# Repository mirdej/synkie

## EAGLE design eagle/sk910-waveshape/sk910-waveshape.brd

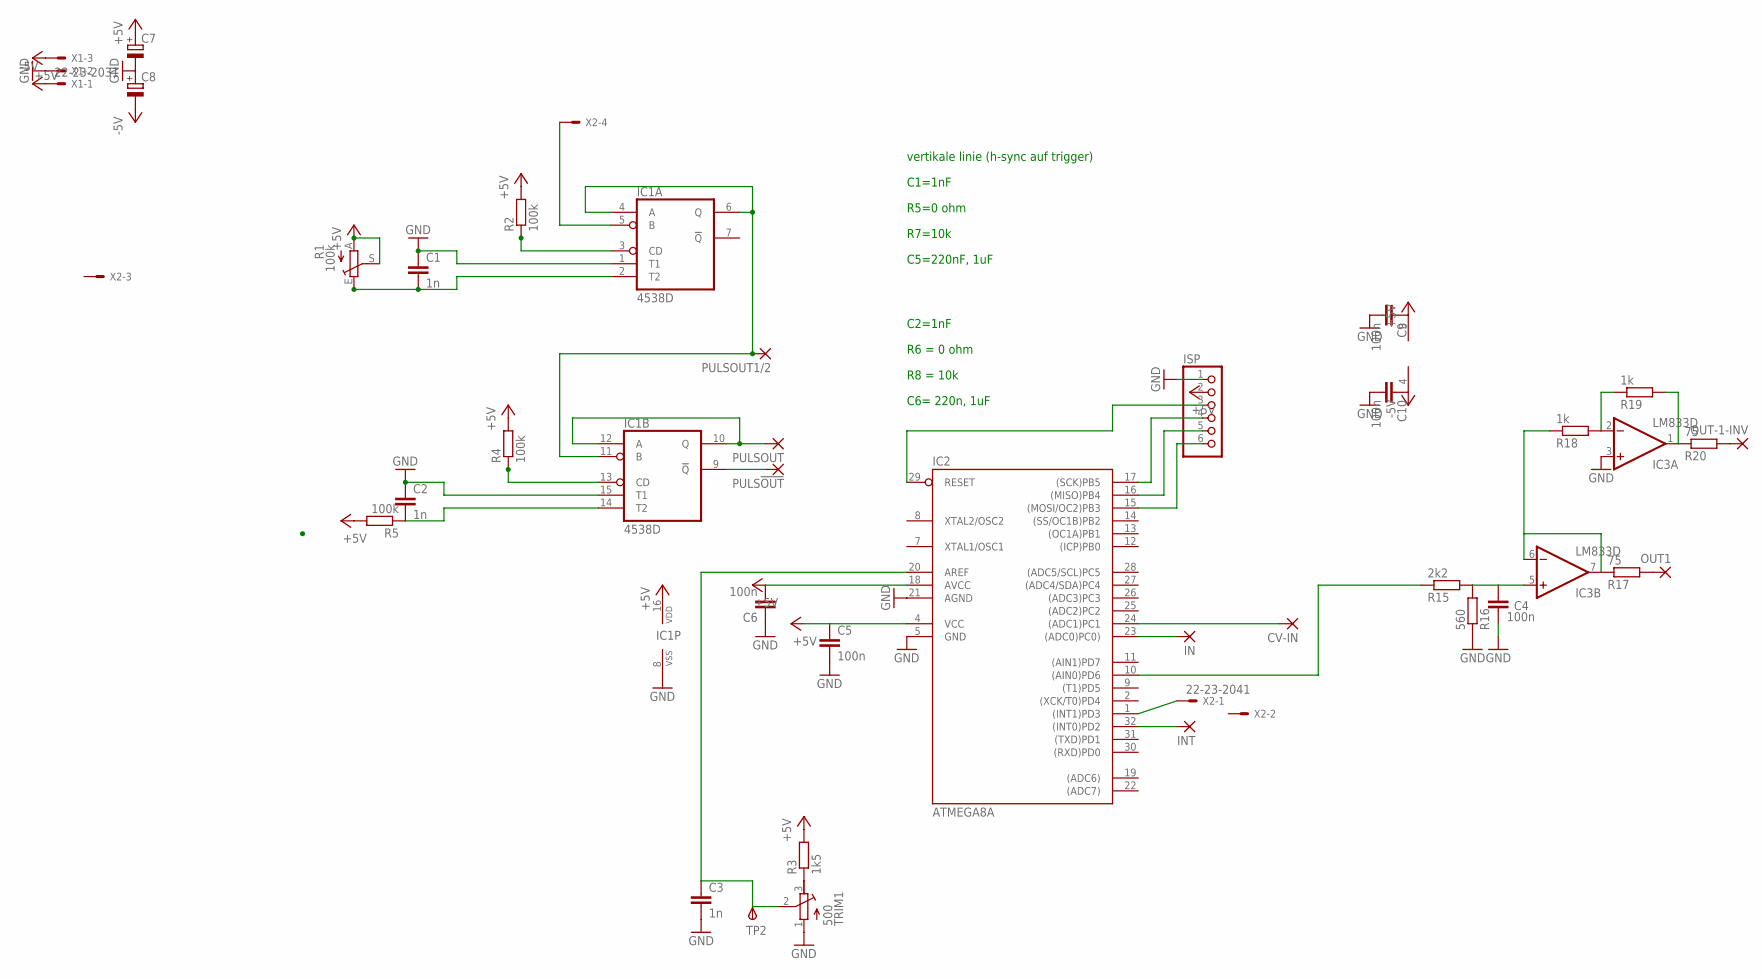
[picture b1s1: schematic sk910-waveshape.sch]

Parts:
C1, C2, C3: 1n; C1206
C4: 100n; C0805
C5: 100n; C1206
C6, C9, C10: 100n; C0603
C7, C8: CPOL-EUCT6032; CT6032
CV-IN: 3,17/1,1
IC1: 4538D; SO16
IC2: ATMEGA8A; TQFP32-08
IC3: LM833D; SO08
IN: 3,17/1,1
INT: 3,17/1,1
ISP: PINHD-1X6; 1X06
OUT1: 3,17/1,1
OUT-1-INV: 3,17/1,1
PULS!OUT: 3,17/1,1
PULSOUT, PULSOUT1/2: 3,17/1,1
R1: 100k; CIP20C-6MM
R2, R4, R5: 100k; R1206
R3: 1k5; R1206
R15: 2k2; R1206
R16: 560; R1206
R17, R20: 75; R1206
R18, R19: 1k; R1206
TP2: TPSPAD1-13; P1-13
TRIM1: 500; RTRIM64Y
X1: 22-23-2031
X2: 22-23-2041

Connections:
+5V: C2.2, C5.1, C6.2, C7.+, C9.1, IC1.14 (T2), IC1.16 (VDD), IC2.4 (VCC), IC2.18 (AVCC), IC3.8 (V+), ISP.2, R1.A, R1.S, R2.2, R3.2, R4.2, R5.1, R5.2, X1.3
-5V: C8.-, C10.1, IC3.4 (V-), X1.1
GND: C1.1, C2.1, C3.2, C4.2, C5.2, C6.1, C7.-, C8.+, C9.2, C10.2, IC1.1 (T1), IC1.8 (VSS), IC1.15 (T1), IC2.5 (GND), IC2.21 (AGND), IC3.3 (+IN), ISP.1, R16.1, TRIM1.1 (E), X1.2
unnamed: IC1.3 (CD), R2.1
unnamed: IC2.32 ((INT0)PD2), INT.1
unnamed: IC1.10 (Q), IC1.12 (A), PULSOUT.1
unnamed: IC1.4 (A), IC1.6 (Q), IC1.11 (B), PULSOUT1/2.1
unnamed: IC2.23 ((ADC0)PC0)), IN.1
unnamed: C1.2, IC1.2 (T2), R1.E
unnamed: IC2.1 ((INT1)PD3), X2.1
unnamed: R3.1, TRIM1.3 (A)
unnamed: CV-IN.1, IC2.24 ((ADC1)PC1)
unnamed: IC2.29 (RESET), ISP.3
unnamed: IC2.17 ((SCK)PB5), ISP.4
unnamed: IC1.13 (CD), R4.1
unnamed: IC1.9 (!Q), PULS!OUT.1
unnamed: IC2.16 ((MISO)PB4), ISP.5
unnamed: IC2.15 ((MOSI/OC2)PB3), ISP.6
unnamed: IC1.5 (B), X2.4
unnamed: IC2.10 ((AIN0)PD6), R15.1
unnamed: C4.1, IC3.5 (+IN), R15.2, R16.2
unnamed: IC3.6 (-IN), IC3.7 (OUT), R17.1, R18.1
unnamed: IC3.2 (-IN), R18.2, R19.1
unnamed: OUT-1-INV.1, R20.2
unnamed: OUT1.1, R17.2
unnamed: IC3.1 (OUT), R19.2, R20.1
unnamed: C3.1, IC2.20 (AREF), TP2.TP, TRIM1.2 (S)

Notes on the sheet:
vertikale linie (h-sync auf trigger)
C1=1nF
R5=0 ohm
R7=10k
C5=220nF, 1uF
C2=1nF
R6 = 0 ohm
R8 = 10k
C6= 220n, 1uF

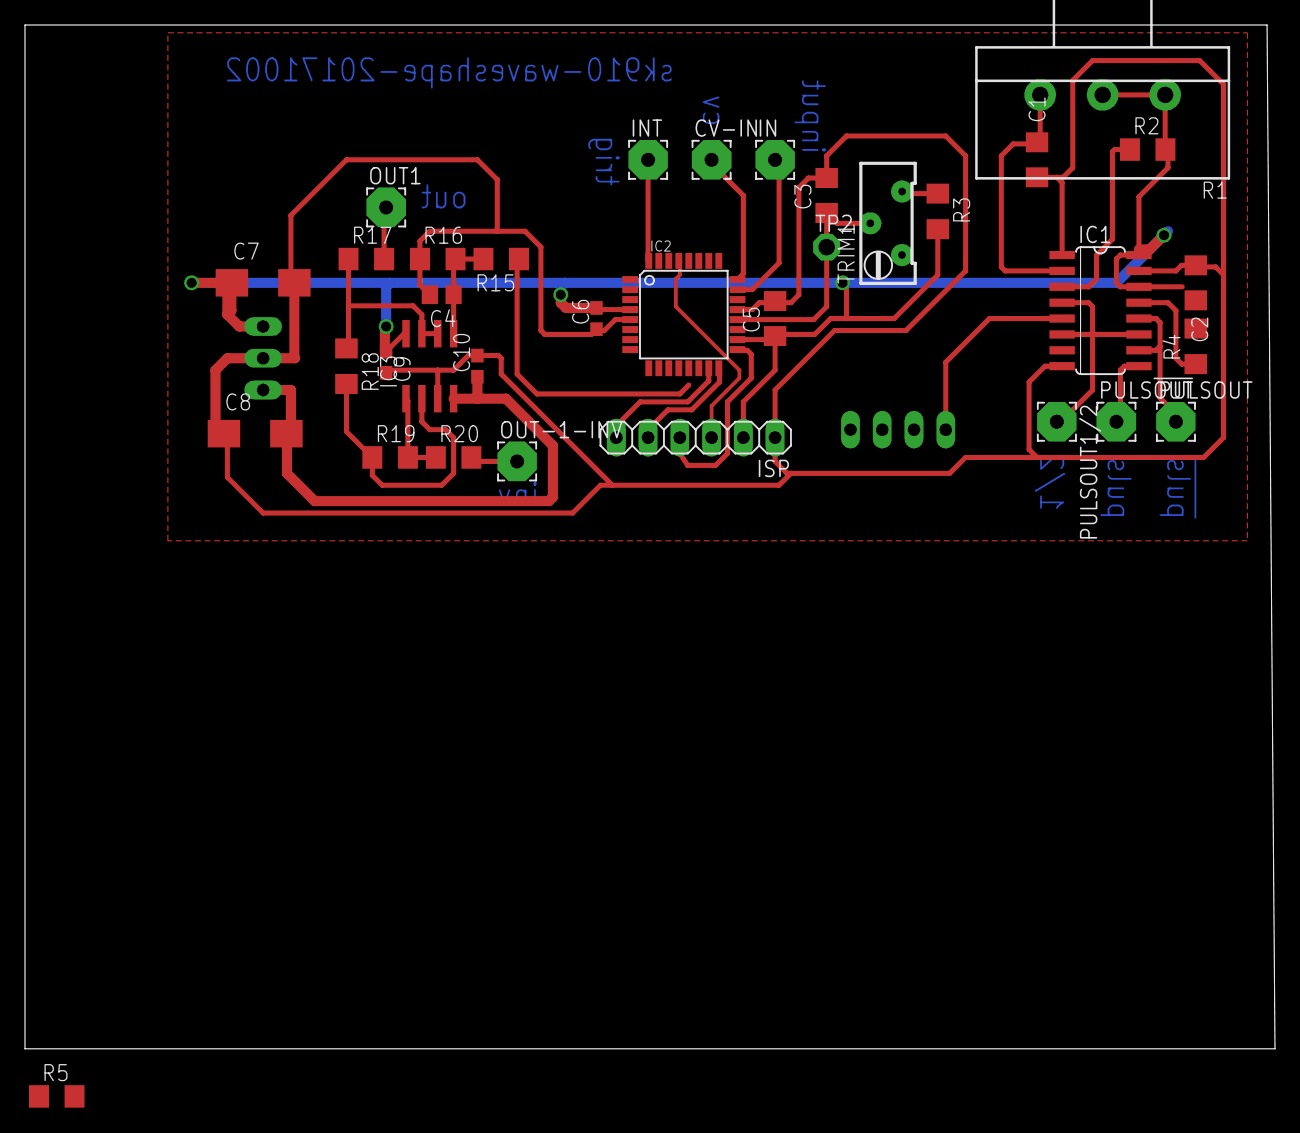
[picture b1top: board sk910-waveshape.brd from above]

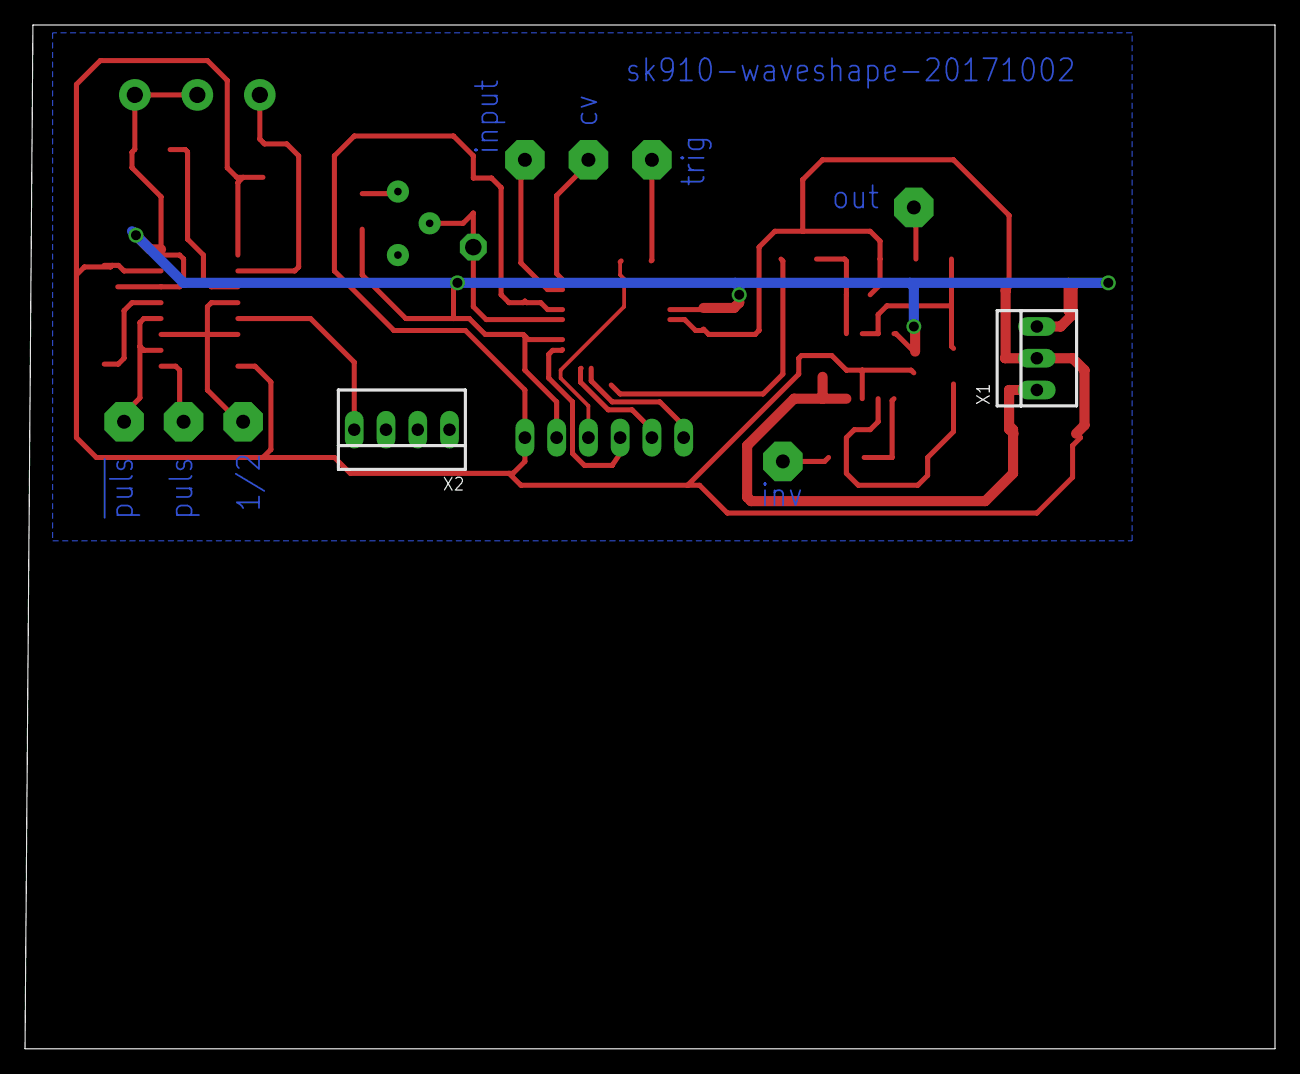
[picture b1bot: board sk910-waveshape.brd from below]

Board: 2 copper layers, 100.0 x 81.9 mm, 37 parts (2 on the bottom side), 27 nets.

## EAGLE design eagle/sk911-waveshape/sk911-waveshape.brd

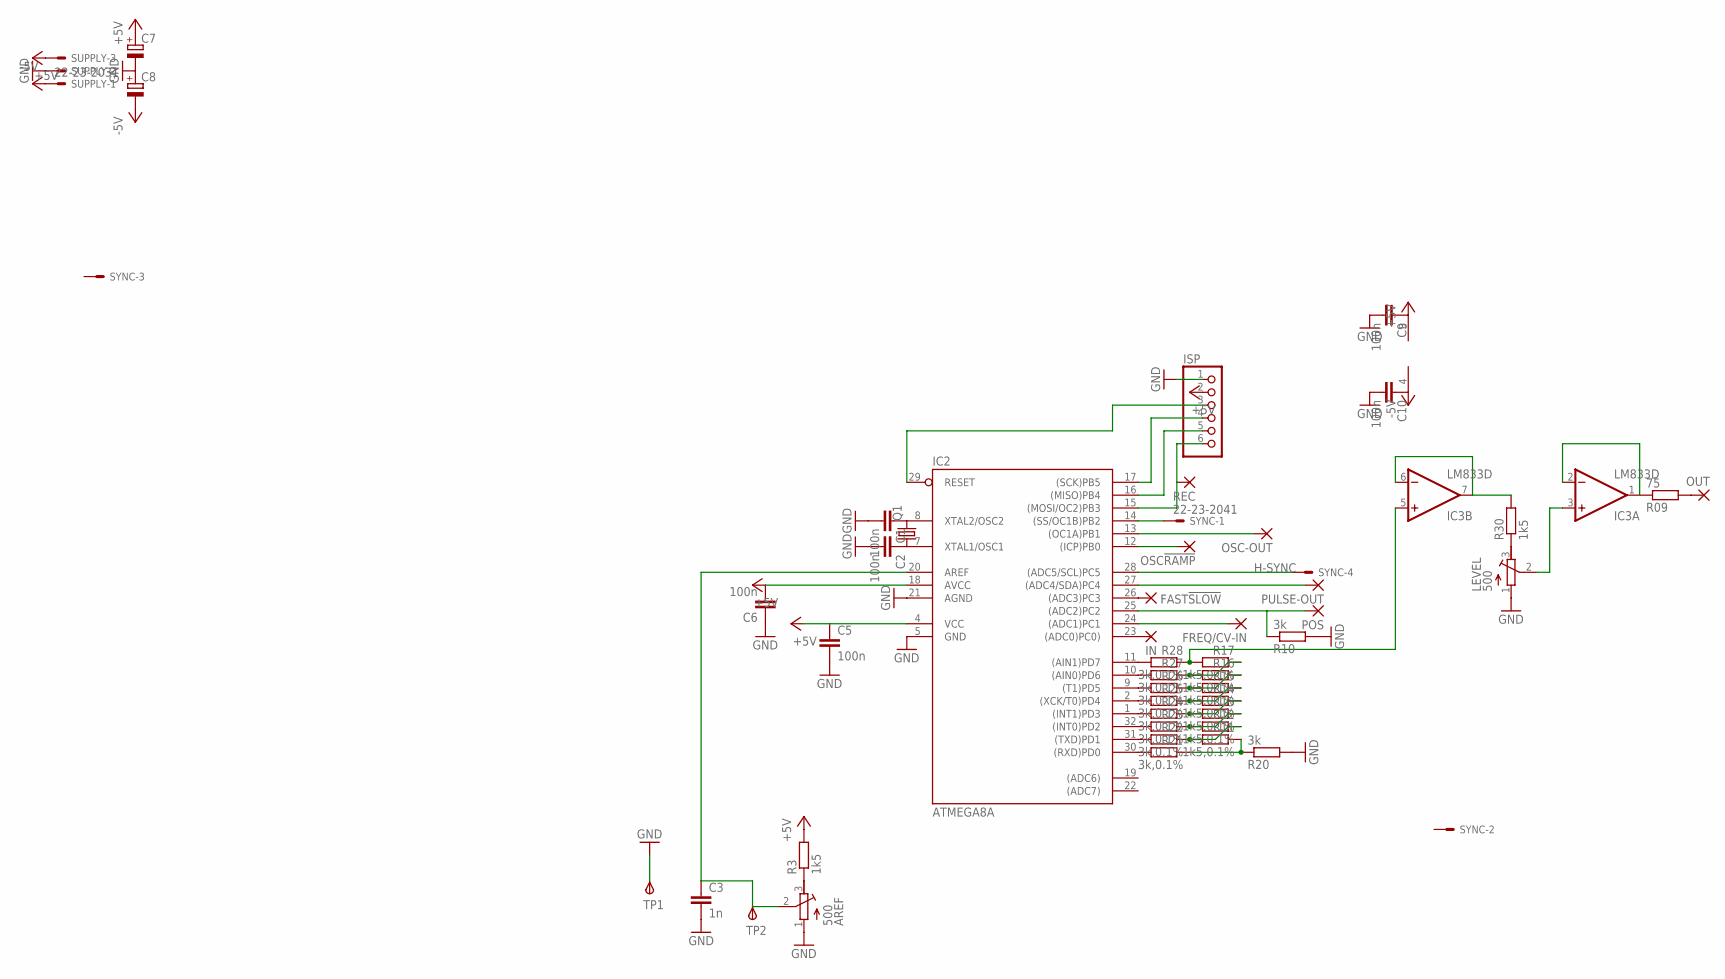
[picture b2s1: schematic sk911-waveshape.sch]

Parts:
AREF: 500; RTRIM64Y
C1, C2: 100n; C0805
C3: 1n; C1206
C5, C6, C9, C10: 100n; C0603
C7, C8: CPOL-EUCT6032; CT6032
FAST!SLOW: 3,17/1,1
FREQ/CV-IN: 3,17/1,1
IC2: ATMEGA8A; TQFP32-08
IC3: LM833D; SO08
IN: 3,17/1,1
ISP: PINHD-1X6; 1X06
LEVEL: 500; RTRIM64Y
OSC!RAMP: 3,17/1,1
OSC-OUT: 3,17/1,1
OUT: 3,17/1,1
POS: 3,17/1,1
PULSE-OUT: 3,17/1,1
Q1: CRYSTALHC49UP; HC49UP
R3, R30: 1k5; R1206
R09: 75; R1206
R10: 3k; R1206
R11, R12, R13, R14, R15, R16, R17: 1k5,0.1%; R0603
R20: 3k; R0603
R21, R22, R23, R24, R25, R26, R27, R28: 3k,0.1%; R0603
REC: 3,17/1,1
SUPPLY: 22-23-2031
SYNC: 22-23-2041
TP1, TP2: TPSPAD1-13; P1-13

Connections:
+5V: C5.1, C6.2, C7.+, C9.1, IC2.4 (VCC), IC2.18 (AVCC), IC3.8 (V+), ISP.2, R3.2, SUPPLY.3
-5V: C8.-, C10.1, IC3.4 (V-), SUPPLY.1
GND: AREF.1 (E), C1.2, C2.2, C3.2, C5.2, C6.1, C7.-, C8.+, C9.2, C10.2, IC2.5 (GND), IC2.21 (AGND), ISP.1, LEVEL.1 (E), R10.2, R20.2, SUPPLY.2, TP1.TP
H-SYNC: IC2.28 ((ADC5/SCL)PC5), SYNC.4
unnamed: C1.1, IC2.8 (XTAL2/OSC2), Q1.2
unnamed: IC2.25 ((ADC2)PC2), POS.1, R10.1
unnamed: C2.1, IC2.7 (XTAL1/OSC1), Q1.1
unnamed: IC2.31 ((TXD)PD1), R22.2
unnamed: IC2.23 ((ADC0)PC0)), IN.1
unnamed: IC2.1 ((INT1)PD3), R24.2
unnamed: IC2.2 ((XCK/T0)PD4), R25.2
unnamed: AREF.3 (A), R3.1
unnamed: FREQ/CV-IN.1, IC2.24 ((ADC1)PC1)
unnamed: IC2.29 (RESET), ISP.3
unnamed: IC2.17 ((SCK)PB5), ISP.4
unnamed: IC2.9 ((T1)PD5), R26.2
unnamed: IC2.10 ((AIN0)PD6), R27.2
unnamed: IC2.16 ((MISO)PB4), ISP.5
unnamed: IC2.15 ((MOSI/OC2)PB3), ISP.6, REC.1
unnamed: IC2.11 ((AIN1)PD7), R28.2
unnamed: IC2.30 ((RXD)PD0), R21.2
unnamed: IC2.13 ((OC1A)PB1), OSC-OUT.1
unnamed: IC2.12 ((ICP)PB0), OSC!RAMP.1
unnamed: IC2.32 ((INT0)PD2), R23.2
unnamed: R11.2, R12.1, R22.1
unnamed: R11.1, R20.1, R21.1
unnamed: R12.2, R13.1, R23.1
unnamed: R13.2, R14.1, R24.1
unnamed: R14.2, R15.1, R25.1
unnamed: R15.2, R16.1, R26.1
unnamed: R16.2, R17.1, R27.1
unnamed: IC3.5 (+IN), R17.2, R28.1
unnamed: IC3.6 (-IN), IC3.7 (OUT), R30.2
unnamed: LEVEL.3 (A), R30.1
unnamed: IC3.1 (OUT), IC3.2 (-IN), R09.1
unnamed: IC3.3 (+IN), LEVEL.2 (S)
unnamed: FAST!SLOW.1, IC2.26 ((ADC3)PC3)
unnamed: IC2.27 ((ADC4/SDA)PC4), PULSE-OUT.1
unnamed: OUT.1, R09.2
unnamed: AREF.2 (S), C3.1, IC2.20 (AREF), TP2.TP
ODD!EVEN: IC2.14 ((SS/OC1B)PB2), SYNC.1

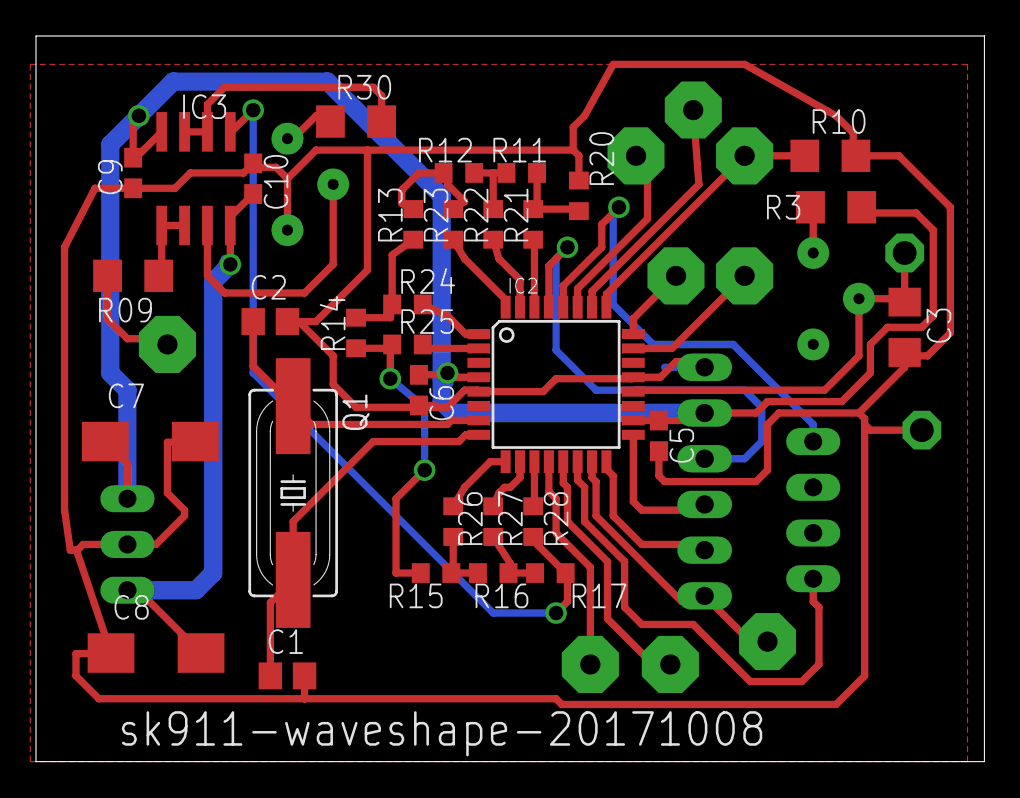
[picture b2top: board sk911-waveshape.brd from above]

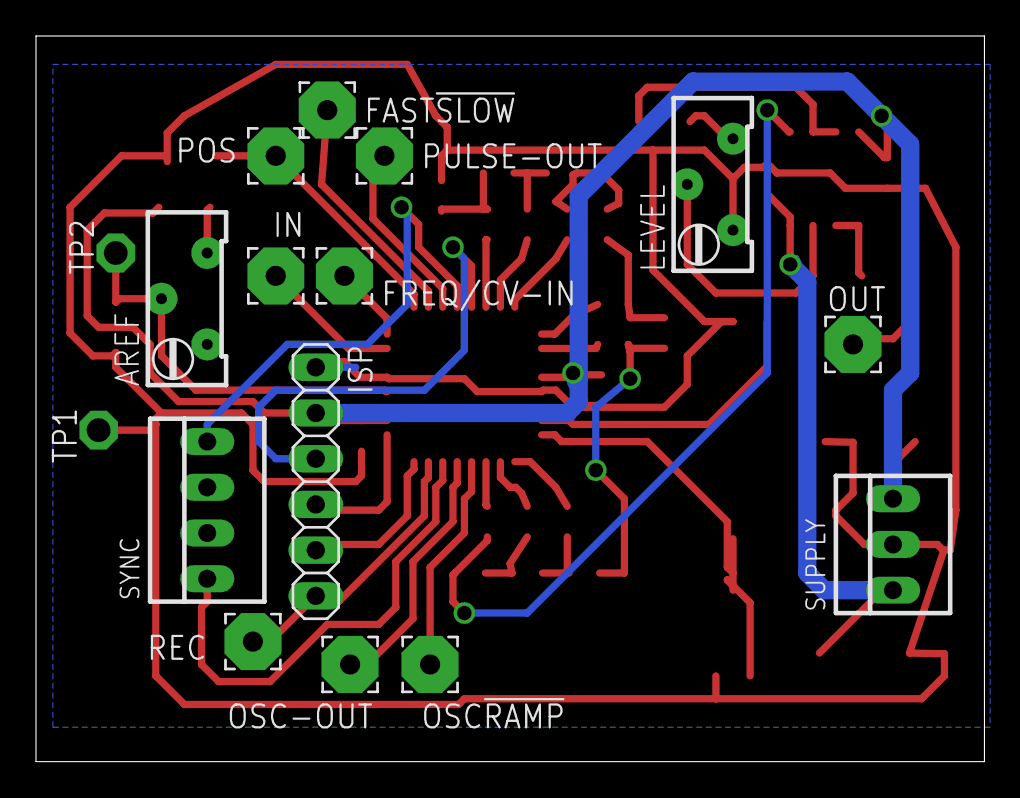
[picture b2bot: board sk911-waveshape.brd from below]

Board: 2 copper layers, 52.7 x 40.3 mm, 48 parts (16 on the bottom side), 41 nets.

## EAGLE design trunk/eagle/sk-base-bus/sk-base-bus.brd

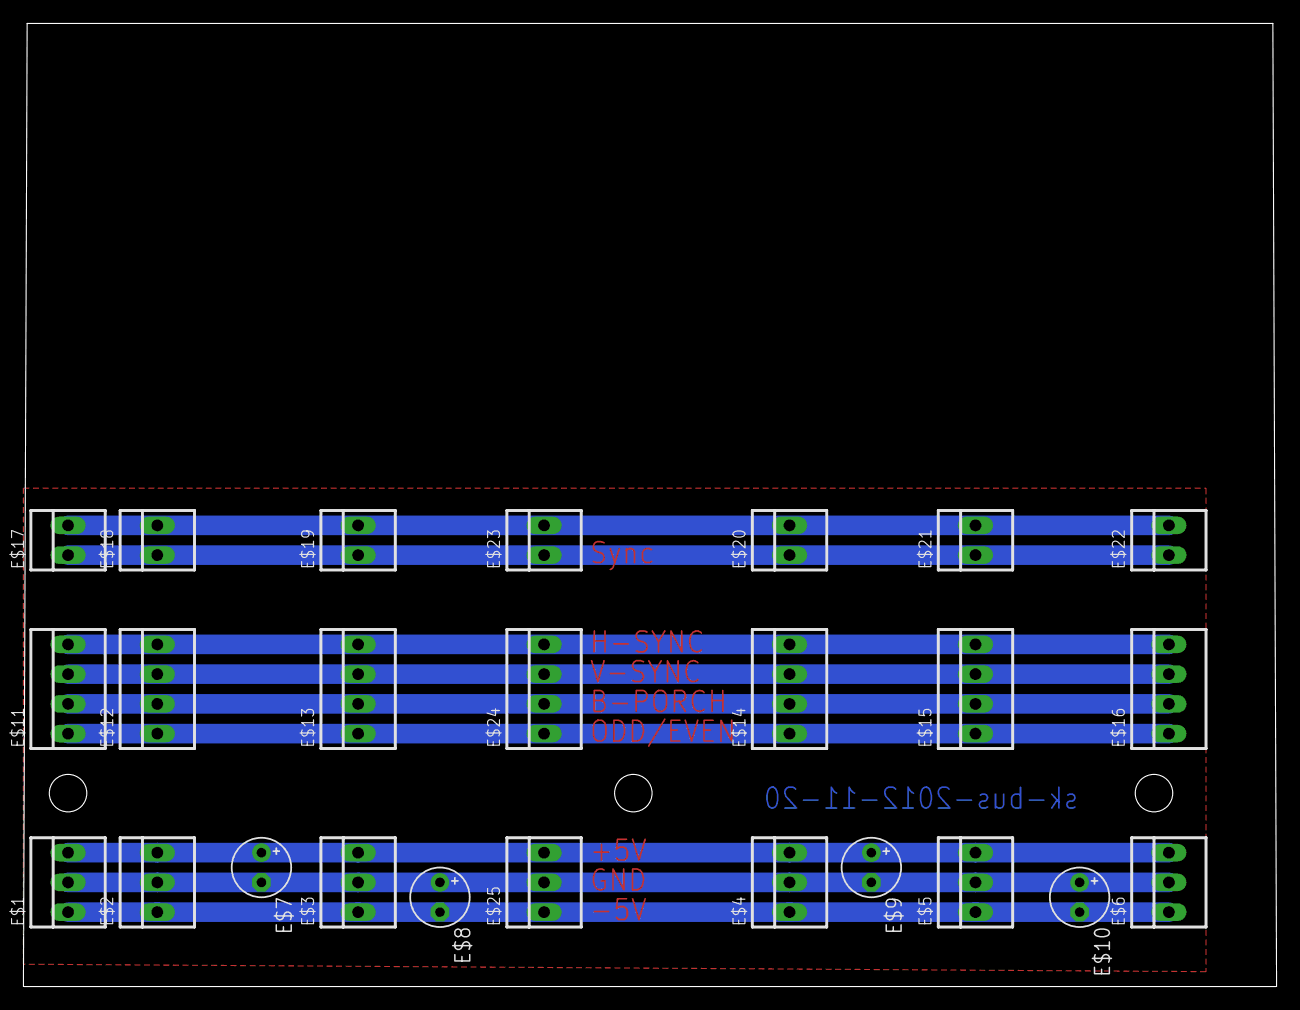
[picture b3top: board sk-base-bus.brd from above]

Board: 2 copper layers, 107.0 x 82.2 mm, 25 parts (0 on the bottom side), 9 nets.

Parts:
E$1, E$2, E$3, E$4, E$5, E$6, E$25: 22-23-2031
E$7, E$8, E$9, E$10: E2,5-5
E$11, E$12, E$13, E$14, E$15, E$16, E$24: 22-23-2041
E$17, E$18, E$19, E$20, E$21, E$22, E$23: 22-23-2021

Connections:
AGND: E$17.2, E$18.2, E$19.2, E$20.2, E$21.2, E$22.2
GND: E$1.2, E$2.2, E$3.2, E$4.2, E$5.2, E$6.2
S$1: E$1.3, E$2.3, E$3.3, E$4.3, E$5.3, E$6.3
S$3: E$1.1, E$2.1, E$3.1, E$4.1, E$5.1, E$6.1
S$5: E$11.4, E$12.4, E$13.4, E$14.4, E$15.4, E$16.4
S$6: E$11.3, E$12.3, E$13.3, E$14.3, E$15.3, E$16.3
S$7: E$11.2, E$12.2, E$13.2, E$14.2, E$15.2, E$16.2
S$8: E$11.1, E$12.1, E$13.1, E$14.1, E$15.1, E$16.1
S$10: E$17.1, E$18.1, E$19.1, E$20.1, E$21.1, E$22.1

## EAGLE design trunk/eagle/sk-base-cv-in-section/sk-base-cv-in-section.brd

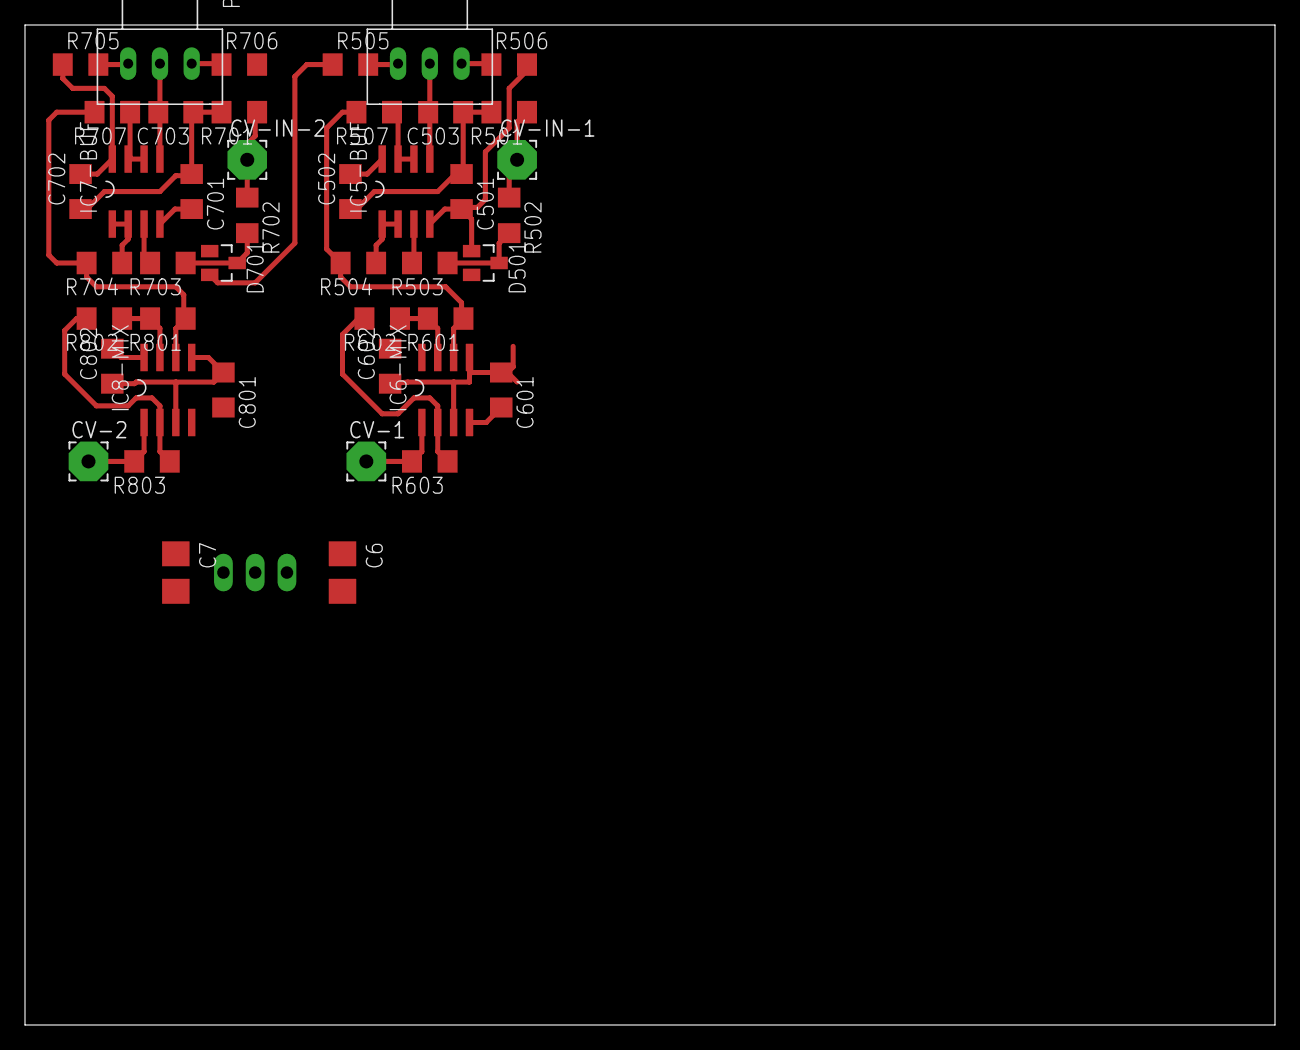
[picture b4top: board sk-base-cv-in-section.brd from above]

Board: 2 copper layers, 100.0 x 80.0 mm, 45 parts (1 on the bottom side), 27 nets.

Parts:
C6, C7: 2u2tantal; CT3528
C501, C502, C503, C601, C602, C701, C702, C703, C801, C802: C1206
CV-1, CV-2: 3,17/1,1
CV-IN-1, CV-IN-2: 3,17/1,1
D501, D701: BAT54S-L44; SOT23
IC5-BUF, IC6-MIX, IC7-BUF, IC8-MIX: MAX4392ESA; SO08
POT10K1: 10k; ALPS_RK09K111
R501, R701: 47k; R1206
R502, R503, R702, R703: 100; R1206
R504, R507, R601, R602, R603, R704, R707, R801, R802, R803: 4k7; R1206
R505, R506, R705, R706: 20k; R1206
U$1: ALPS_RK09K111_HOHNE-FüSSE; ALPS_RK09K111
X1: 22-23-2031

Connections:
+5V: C6.+, C502.2, C602.2, C702.2, C802.2, D501.2, D701.2, IC5-BUF.8, IC6-MIX.8, IC7-BUF.8, IC8-MIX.8, R505.1, R705.1, X1.3
-5V: C7.-, C501.2, C601.2, C701.2, C801.2, D501.1, D701.1, IC5-BUF.4, IC6-MIX.4, IC7-BUF.4, IC8-MIX.4, R506.2, R706.2, X1.1
GND: C6.-, C7.+, C501.1, C502.1, C503.1, C601.1, C602.1, C701.1, C702.1, C703.1, C801.1, C802.1, IC6-MIX.3, IC6-MIX.5, IC8-MIX.3, IC8-MIX.5, R501.2, R701.2, X1.2
unnamed: C503.2, IC5-BUF.5, U$1.2
unnamed: R506.1, U$1.1
unnamed: R505.2, U$1.3
unnamed: CV-IN-1.1, R501.1, R502.1
unnamed: D501.3, R502.2, R503.1
unnamed: IC5-BUF.6, IC5-BUF.7, R507.1
unnamed: IC5-BUF.3, R503.2
unnamed: IC5-BUF.1, IC5-BUF.2, R504.1
unnamed: IC6-MIX.6, R504.2, R507.2, R601.1
unnamed: IC6-MIX.7, R601.2, R602.1
unnamed: IC6-MIX.2, R602.2, R603.1
unnamed: CV-1.1, IC6-MIX.1, R603.2
unnamed: CV-IN-2.1, R701.1, R702.1
unnamed: D701.3, R702.2, R703.1
unnamed: IC7-BUF.3, R703.2
unnamed: IC7-BUF.1, IC7-BUF.2, R704.1
unnamed: IC7-BUF.6, IC7-BUF.7, R707.1
unnamed: IC8-MIX.6, R704.2, R707.2, R801.1
unnamed: IC8-MIX.7, R801.2, R802.1
unnamed: IC8-MIX.2, R802.2, R803.1
unnamed: CV-2.1, IC8-MIX.1, R803.2
unnamed: C703.2, IC7-BUF.5, POT10K1.2
unnamed: POT10K1.1, R706.1
unnamed: POT10K1.3, R705.2

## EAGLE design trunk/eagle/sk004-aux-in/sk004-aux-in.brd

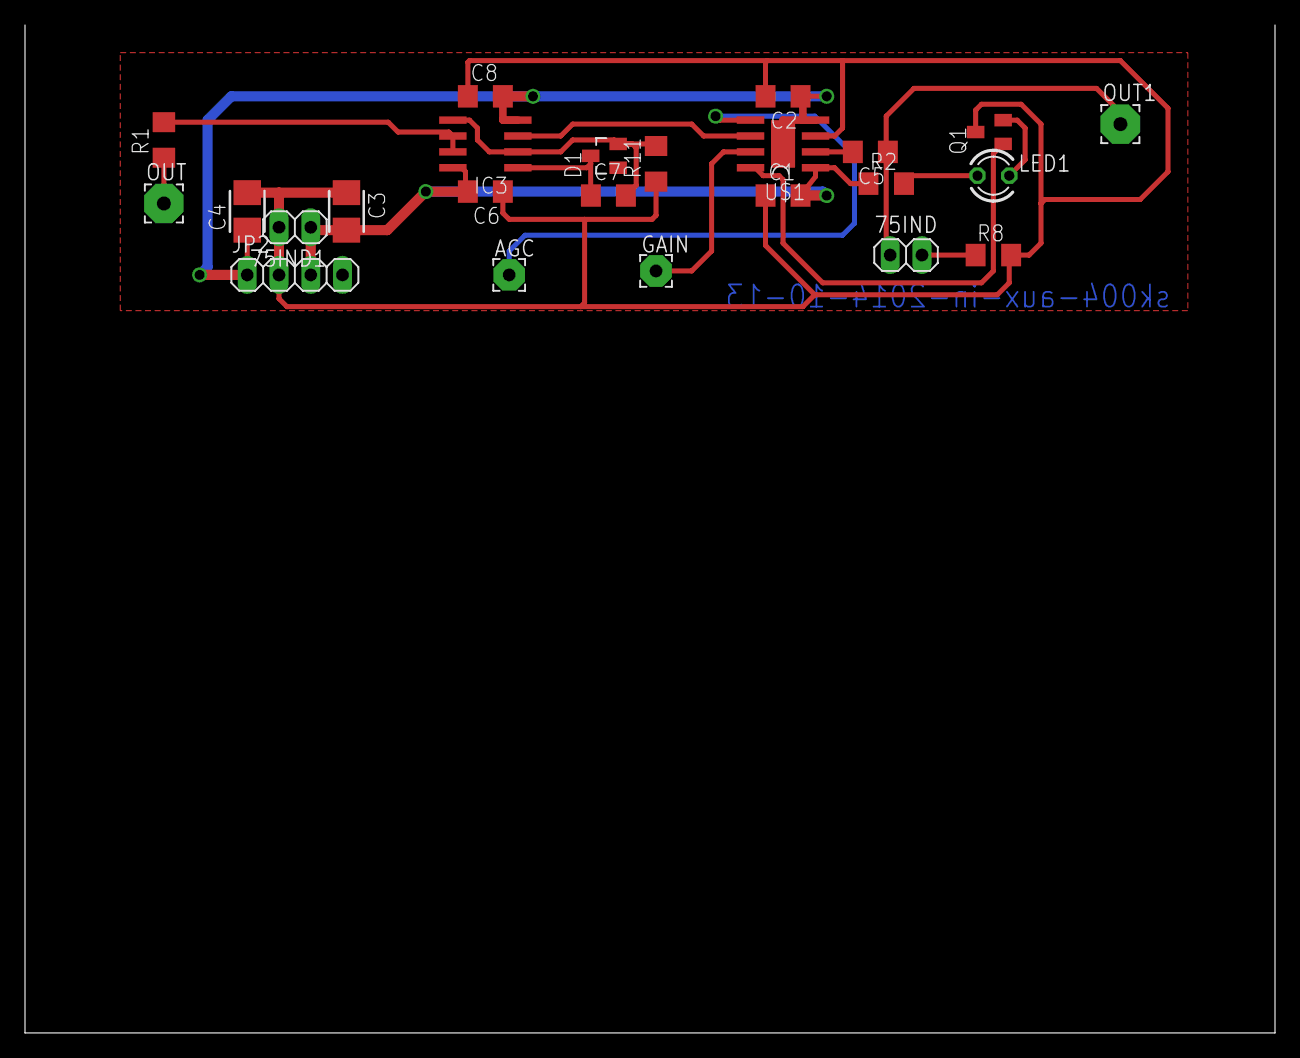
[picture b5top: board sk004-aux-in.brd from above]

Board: 2 copper layers, 100.0 x 80.6 mm, 24 parts (0 on the bottom side), 16 nets.

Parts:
75IND, 75IND1: 1X02
AGC: 2,54/1,0
C1, C2: C1206
C3, C4: 2u2tantal; CT3528
C5: 1u; C1206
C6, C8: 100n; C1206
C7: 10p; C1206
D1: BAT54S-L44; SOT23
GAIN: 2,54/1,0
IC3: LM833D; SO08
JP2: 1X04
LED1: LED3MM
OUT, OUT1: 3,17/1,1
Q1: BC857ASMD; SOT23-BEC
R1, R8: 75; R1206
R2: 300; R1206
R11: 1k; R1206
U$1: MAX7450; SO08-EXP

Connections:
+5V: 75IND1.1, C1.2, C3.+, C6.2, IC3.8, JP2.3, R2.1, U$1.1
-5V: C2.1, C4.-, C8.2, IC3.4, JP2.1, U$1.4, U$1.EXP
GND: 75IND1.2, C1.1, C2.2, C3.-, C4.+, C6.1, C8.1, JP2.2, Q1.C, R8.2, R11.1, U$1.3
unnamed: 75IND.2, R8.1
unnamed: 75IND.1, C5.1, OUT1.1
unnamed: IC3.3, U$1.6
unnamed: GAIN.1, U$1.7
unnamed: AGC.1, U$1.5
unnamed: LED1.A, R2.2
unnamed: Q1.B, U$1.8
unnamed: C5.2, U$1.2
unnamed: LED1.K, Q1.E
unnamed: IC3.6, IC3.7, R1.2
unnamed: OUT.1, R1.1
unnamed: C7.1, D1.3, IC3.1
unnamed: C7.2, D1.2, IC3.2, IC3.5, R11.2

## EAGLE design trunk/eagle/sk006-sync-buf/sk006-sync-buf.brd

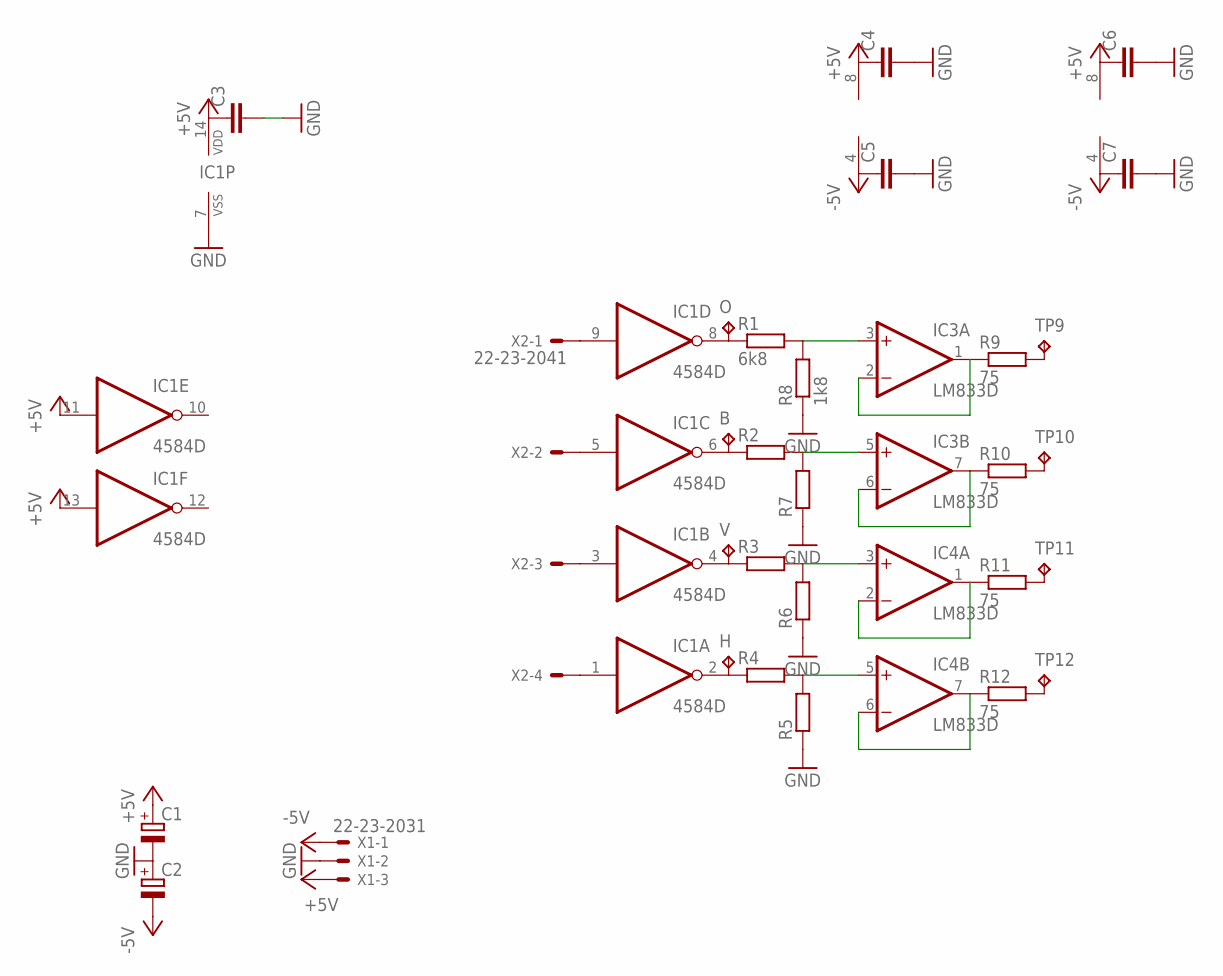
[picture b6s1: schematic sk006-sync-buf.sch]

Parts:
B: TPB2,54; B2,54
C1, C2: CPOL-EUE2.5-7; E2,5-7
C3, C4, C5, C6, C7: C-EUC1206; C1206
H: TPB2,54; B2,54
IC1: 4584D; SO14
IC3, IC4: LM833D; SO08
O: TPB2,54; B2,54
R1: 6k8; R1206
R2, R3, R4, R5, R6, R7: R-EU_R1206; R1206
R8: 1k8; R1206
R9, R10, R11, R12: 75; R1206
TP9, TP10, TP11, TP12: TPB2,54; B2,54
V: TPB2,54; B2,54
X1: 22-23-2031
X2: 22-23-2041

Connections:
+5V: C1.+, C3.1, C4.1, C6.1, IC1.11 (I), IC1.13 (I), IC1.14 (VDD), IC3.8 (V+), IC4.8 (V+), X1.3
-5V: C2.-, C5.1, C7.1, IC3.4 (V-), IC4.4 (V-), X1.1
GND: C1.-, C2.+, C3.2, C4.2, C5.2, C6.2, C7.2, IC1.7 (VSS), R5.1, R6.1, R7.1, R8.1, X1.2
unnamed: IC1.5 (I), X2.2
unnamed: IC1.9 (I), X2.1
unnamed: IC1.3 (I), X2.3
unnamed: IC1.1 (I), X2.4
unnamed: IC1.8 (O), O.TP, R1.1
unnamed: B.TP, IC1.6 (O), R2.1
unnamed: IC1.4 (O), R3.1, V.TP
unnamed: H.TP, IC1.2 (O), R4.1
unnamed: IC4.5 (+IN), R4.2, R5.2
unnamed: IC4.3 (+IN), R3.2, R6.2
unnamed: IC3.5 (+IN), R2.2, R7.2
unnamed: IC3.3 (+IN), R1.2, R8.2
unnamed: IC3.1 (OUT), IC3.2 (-IN), R9.1
unnamed: IC3.6 (-IN), IC3.7 (OUT), R10.1
unnamed: IC4.1 (OUT), IC4.2 (-IN), R11.1
unnamed: IC4.6 (-IN), IC4.7 (OUT), R12.1
unnamed: R9.2, TP9.TP
unnamed: R10.2, TP10.TP
unnamed: R11.2, TP11.TP
unnamed: R12.2, TP12.TP

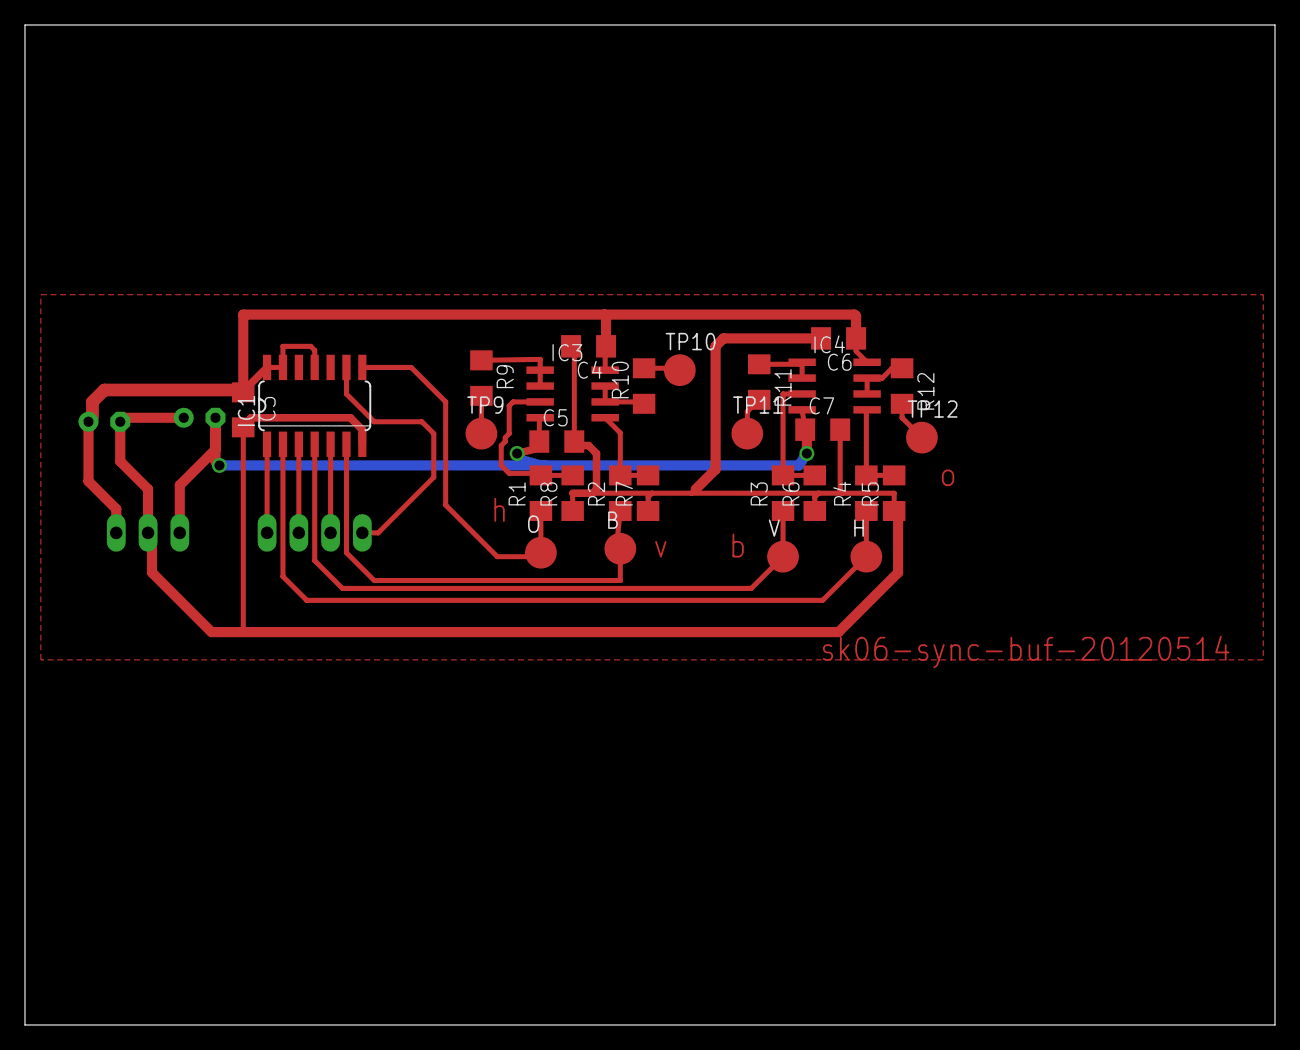
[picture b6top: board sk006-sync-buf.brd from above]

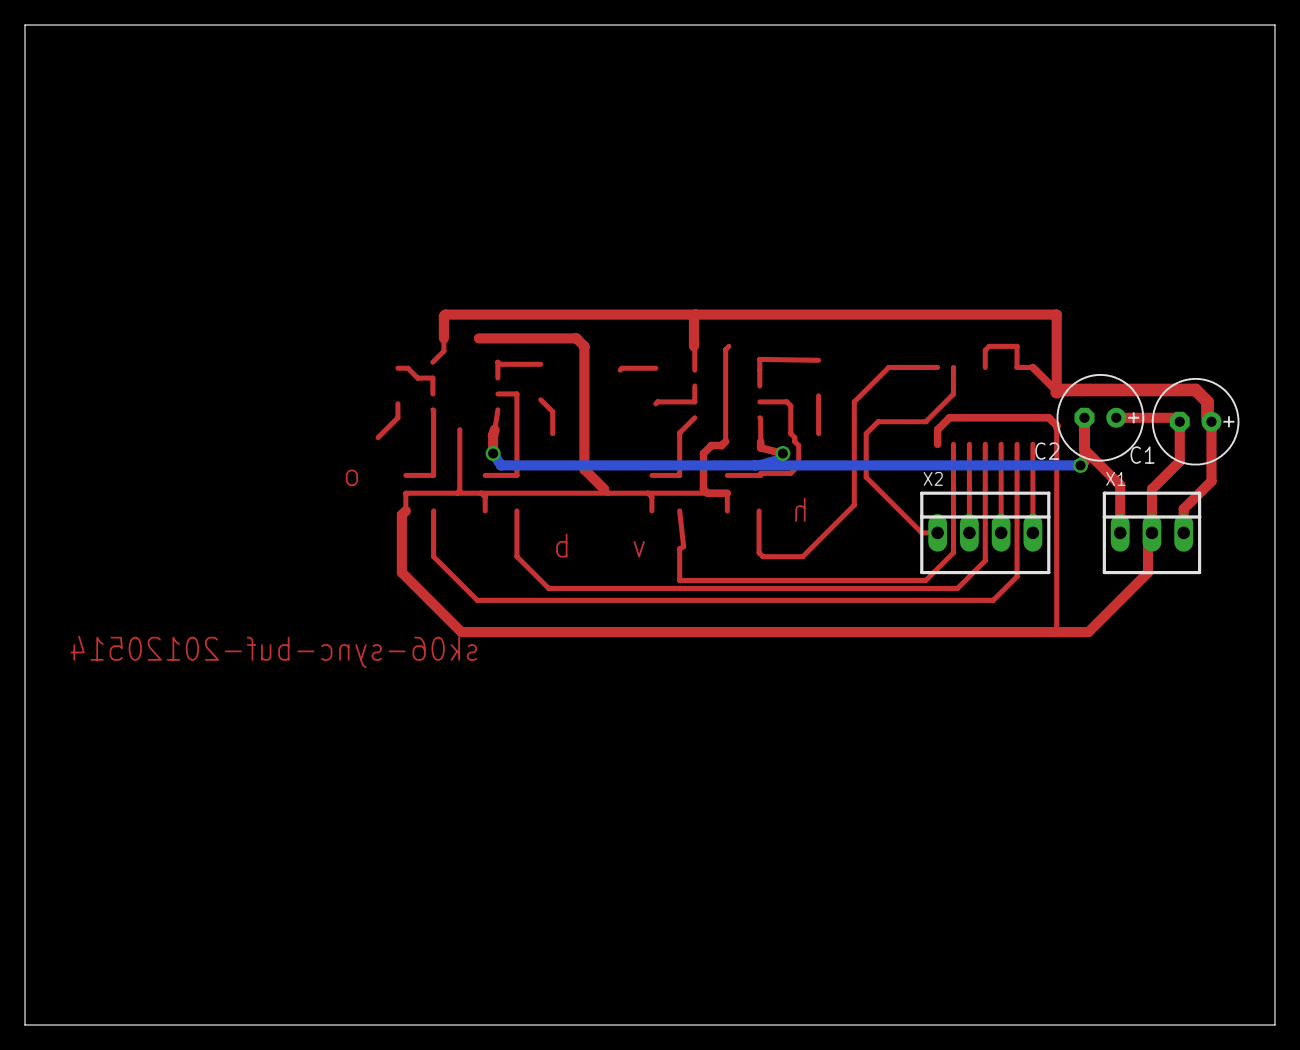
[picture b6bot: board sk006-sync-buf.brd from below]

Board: 2 copper layers, 100.0 x 80.0 mm, 32 parts (4 on the bottom side), 23 nets.
